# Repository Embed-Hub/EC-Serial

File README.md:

# EC-Serial

Framework compatible expansion card based on [Olimex's USB Serial L](https://github.com/OLIMEX/USB-SERIAL-L) schematic, and Josh Cook's USB UART [project](https://github.com/jyancat/UART-Expansion-Card)

# License
Olimex files are available under GPL v3 - so are these.

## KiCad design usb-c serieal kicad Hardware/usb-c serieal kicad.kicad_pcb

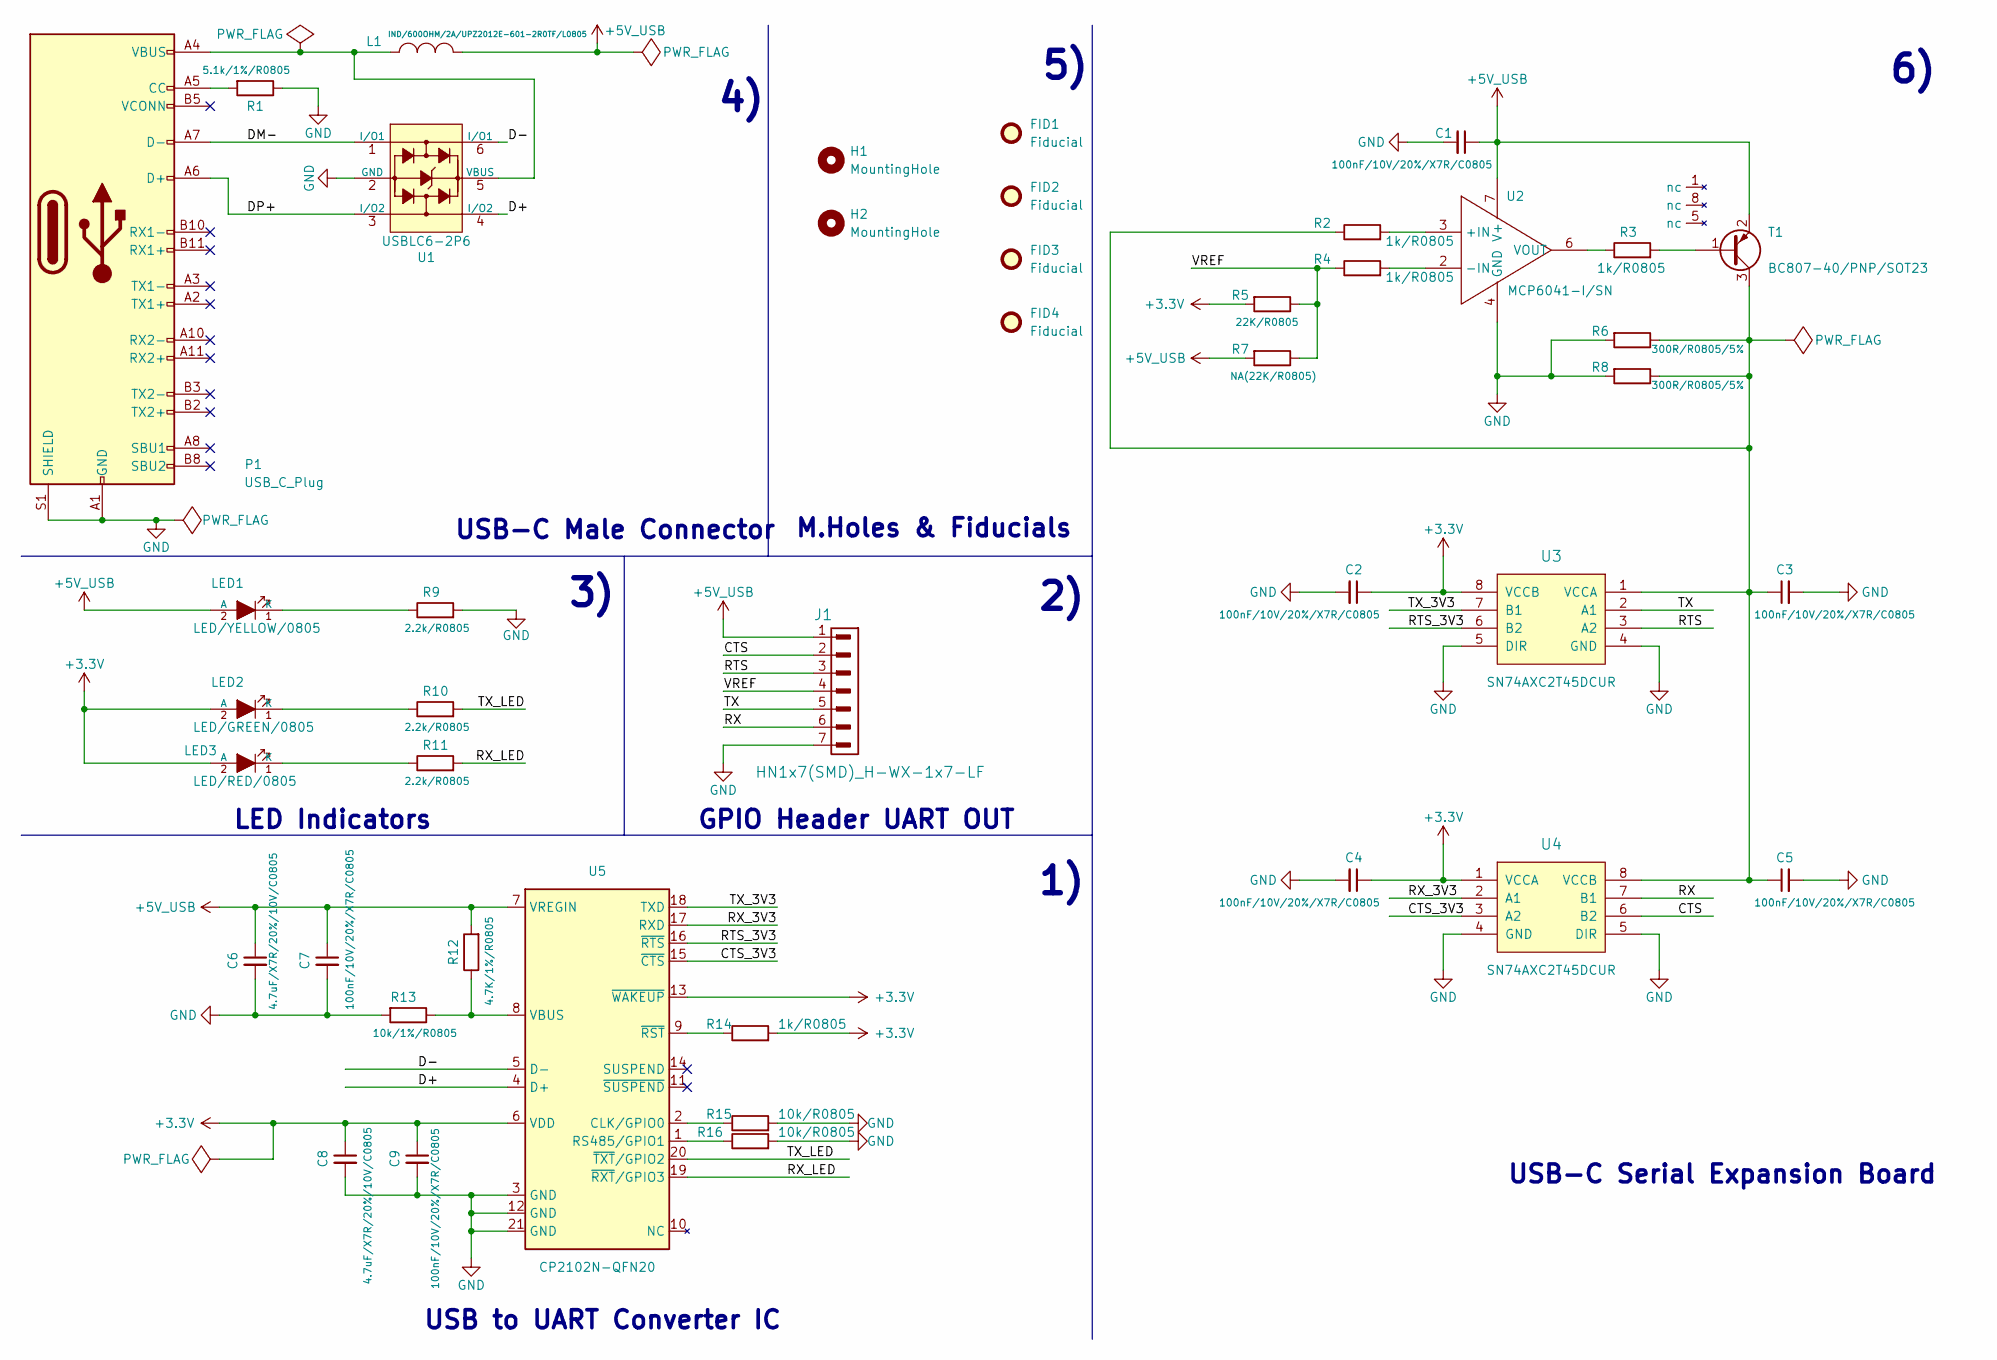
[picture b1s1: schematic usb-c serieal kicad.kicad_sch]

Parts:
C1, C2, C3, C4, C5, C7, C9: 100nF/10V/20%/X7R/C0805; C_0805_2012Metric_Pad1.18x1.45mm_HandSolder
C6, C8: 4.7uF/X7R/20%/10V/C0805; C_0805_2012Metric_Pad1.18x1.45mm_HandSolder
FID1, FID2, FID3, FID4: Fiducial; Fiducial_0.5mm_Mask1mm
H1, H2: MountingHole; MountingHole_2.2mm_M2
J1: HN1x7(SMD)_H-WX-1x7-LF; PinHeader_1x07_P2.54mm_Horizontal
L1: IND/600OHM/2A/UPZ2012E-601-2R0TF/L0805; L_0805_2012Metric_Pad1.15x1.40mm_HandSolder
LED1: LED/YELLOW/0805; LED_0805_2012Metric_Pad1.15x1.40mm_HandSolder
LED2: LED/GREEN/0805; LED_0805_2012Metric_Pad1.15x1.40mm_HandSolder
LED3: LED/RED/0805; LED_0805_2012Metric_Pad1.15x1.40mm_HandSolder
P1: USB_C_Plug; USB_C_Plug_Molex_105444
R1: 5.1k/1%/R0805; R_0805_2012Metric_Pad1.20x1.40mm_HandSolder
R2, R3, R4, R14: 1k/R0805; R_0805_2012Metric_Pad1.20x1.40mm_HandSolder
R5: 22K/R0805; R_0805_2012Metric_Pad1.20x1.40mm_HandSolder
R6, R8: 300R/R0805/5%; R_0805_2012Metric_Pad1.20x1.40mm_HandSolder
R7: NA(22K/R0805); R_0805_2012Metric_Pad1.20x1.40mm_HandSolder
R9, R10, R11: 2.2k/R0805; R_0805_2012Metric_Pad1.20x1.40mm_HandSolder
R12: 4.7K/1%/R0805; R_0805_2012Metric_Pad1.20x1.40mm_HandSolder
R13: 10k/1%/R0805; R_0805_2012Metric_Pad1.20x1.40mm_HandSolder
R15, R16: 10k/R0805; R_0805_2012Metric_Pad1.20x1.40mm_HandSolder
T1: BC807-40/PNP/SOT23; TSOT-23
U1: USBLC6-2P6; SOT-666
U2: MCP6041-I/SN; SOIC-8_3.9x4.9mm_P1.27mm
U3, U4: SN74AXC2T45DCUR; VSSOP-8_2.3x2mm_P0.5mm
U5: CP2102N-QFN20; SiliconLabs_QFN-20-1EP_3x3mm_P0.5mm_EP1.8x1.8mm

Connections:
+3.3V: C2.1, C4.1, C8.1, C9.1, LED2.2 (A), LED3.2 (A), R5.2, R14.2, U3.8 (VCCB), U4.1 (VCCA), U5.6 (VDD), U5.13 (~WAKEUP)
+5V_USB: C1.1, C6.1, C7.1, J1.1, L1.2, LED1.2 (A), R7.2, R12.2, T1.2 (E), U2.7 (V+), U5.7 (VREGIN)
/CTS: J1.2, U4.6 (B2)
/CTS_3V3: U4.3 (A2), U5.15 (~CTS)
/D+: U1.4 (I/O2), U5.4 (D+)
/D-: U1.6 (I/O1), U5.5 (D-)
/DM-: P1.A7 (D-), U1.1 (I/O1)
/DP+: P1.A6 (D+), U1.3 (I/O2)
/RTS: J1.3, U3.3 (A2)
/RTS_3V3: U3.6 (B2), U5.16 (~RTS)
/RX: J1.6, U4.7 (B1)
/RX_3V3: U4.2 (A1), U5.17 (RXD)
/RX_LED: R11.2, U5.19 (~RXT/GPIO3)
/TX: J1.5, U3.2 (A1)
/TX_3V3: U3.7 (B1), U5.18 (TXD)
/TX_LED: R10.2, U5.20 (~TXT/GPIO2)
/VREF: J1.4, R4.1, R5.1, R7.1
GND: C1.2, C2.2, C3.2, C4.2, C5.2, C6.2, C7.2, C8.2, C9.2, J1.7, P1.A1 (GND), P1.A12 (GND), P1.B1 (GND), P1.B12 (GND), P1.S1 (SHIELD), R1.1, R6.2, R8.2, R9.2, R13.2, R15.2, R16.2, U1.2 (GND), U2.4 (GND), U3.4 (GND), U3.5 (DIR), U4.4 (GND), U4.5 (DIR), U5.3 (GND), U5.12 (GND), U5.21 (GND)
unnamed: LED1.1 (K), R9.1
unnamed: LED2.1 (K), R10.1
unnamed: LED3.1 (K), R11.1
unnamed: P1.A5 (CC), R1.2
unnamed: R3.2, T1.1 (B)
unnamed: C3.1, C5.1, R2.1, R6.1, R8.1, T1.3 (C), U3.1 (VCCA), U4.8 (VCCB)
unnamed: L1.1, P1.A4 (VBUS), P1.A9 (VBUS), P1.B4 (VBUS), P1.B9 (VBUS), U1.5 (VBUS)
unnamed: R2.2, U2.3 (+IN)
unnamed: R4.2, U2.2 (-IN)
unnamed: R3.1, U2.6 (VOUT)
unnamed: R15.1, U5.2 (CLK/GPIO0)
unnamed: R16.1, U5.1 (RS485/GPIO1)
unnamed: R12.1, R13.1, U5.8 (VBUS)
unnamed: R14.1, U5.9 (~RST)

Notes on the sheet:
USB-C Serial Expansion Board
USB-C Male Connector
LED Indicators
GPIO Header UART OUT
M.Holes & Fiducials
USB to UART Converter IC

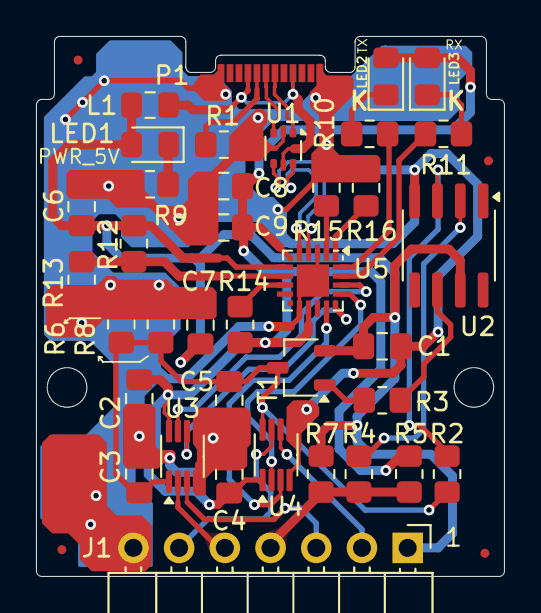
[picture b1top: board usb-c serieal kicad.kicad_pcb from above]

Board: 2 copper layers, 26.0 x 30.0 mm, 43 parts (0 on the bottom side), 32 nets.

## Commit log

2025-09-03 Initial commit
    Design Files
    Gerber files
    Step file
    iBOM file
    Github commit 03-09-2025 V0.0.1 USB-C to Serial Expansion Board kicad files
2025-09-03 Create LICENSE
